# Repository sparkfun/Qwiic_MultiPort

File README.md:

Qwiic MultiPort
========================================

[*SparkFun Qwiic MultiPort (BOB-18012)*](https://www.sparkfun.com/products/18012)

Qwiic is a very efficient way to quickly prototype an idea but not all Qwiic-enabled devices have two ports. The SparkFun Qwiic MultiPort adds additional ports to boards that have only one Qwiic port on the I2C bus. Once added, you can use it as a hub to add as many I2C devices to the bus as you need! Included are mounting holes so that the board can be secured to any system.

Repository Contents
-------------------

* **/Hardware** - Eagle design files (.brd, .sch)
* **/Production** - Production panel files (.brd)

Documentation
--------------
* **[Hookup Guide](https://learn.sparkfun.com/tutorials/1659)**

Product Versions
----------------
* [BOB-18012](https://www.sparkfun.com/products/18012) - Initial Release

License Information
-------------------

This product is _**open source**_! 

Please review the LICENSE.md file for license information. 

If you have any questions or concerns on licensing, please contact technical support on our [SparkFun forums](https://forum.sparkfun.com/viewforum.php?f=152).

Distributed as-is; no warranty is given.

- Your friends at SparkFun.

_<COLLABORATION CREDIT>_

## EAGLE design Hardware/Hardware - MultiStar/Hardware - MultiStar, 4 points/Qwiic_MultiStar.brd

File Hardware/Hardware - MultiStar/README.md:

Qwiic MultiStar
========================================

[*SparkFun Qwiic MultiStar (BOB-?????)*](https://www.sparkfun.com/news/3803)

The MultiStar was designed for April Fools' Day! This board functions like the MultiPort but with an additional Qwiic connector. The board is also shaped like a Ninja star! The following folders include the Eagle files for the MultiStar. For more information, check out the blog post under "[A Sneak Preview of Our Latest Qwiic Product](https://www.sparkfun.com/news/3803)."

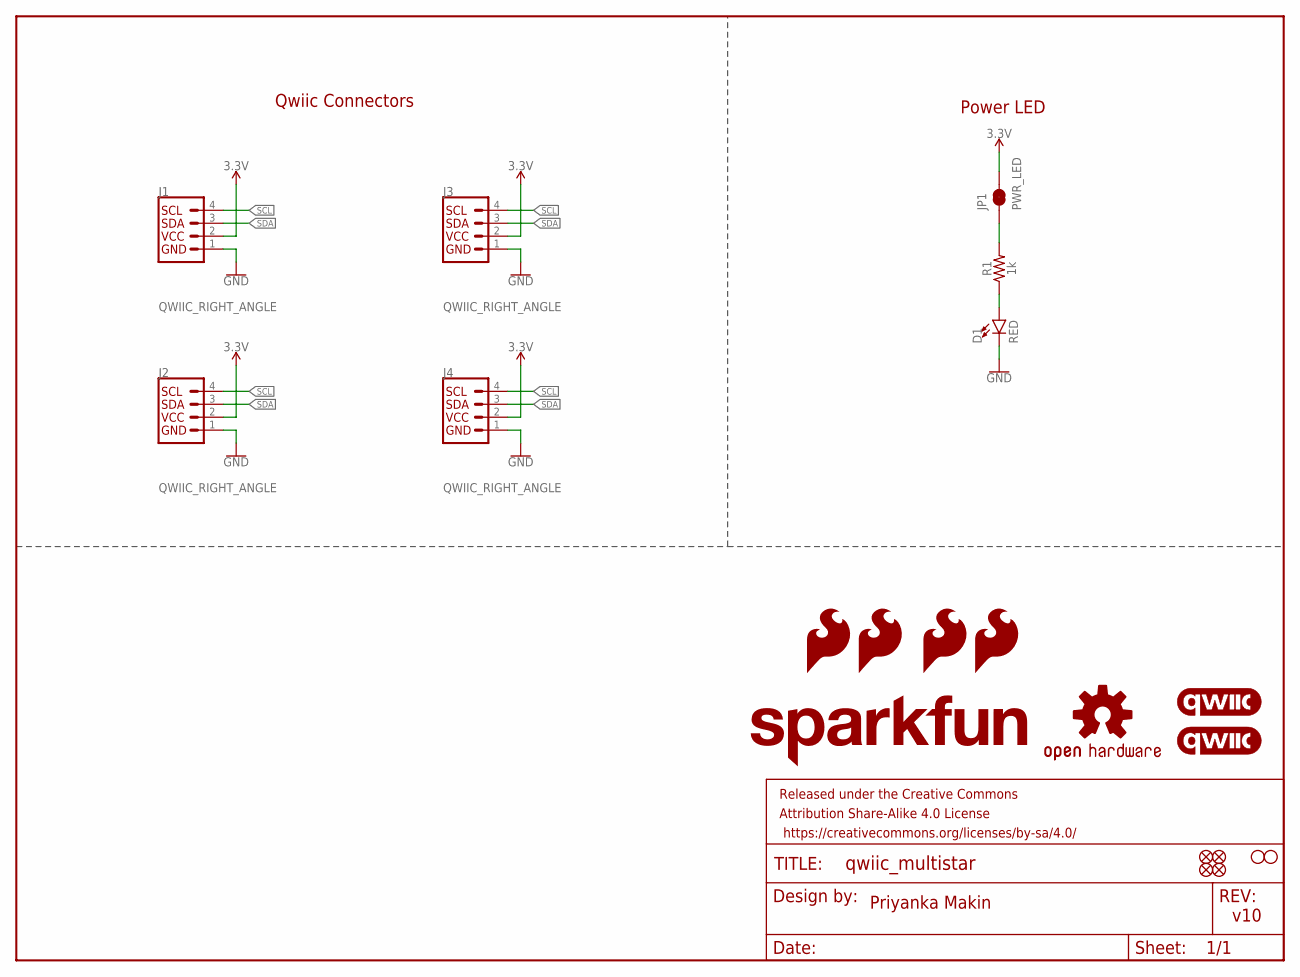
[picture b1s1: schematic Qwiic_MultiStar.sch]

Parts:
D1: RED; LED-0603
FD1, FD2, FD3, FD4: FIDUCIAL1X2; FIDUCIAL-1X2
FRAME1: FRAME-LETTER; CREATIVE_COMMONS
H1, H2: STAND-OFFTIGHT; STAND-OFF-TIGHT
J1, J2, J3, J4: QWIIC_RIGHT_ANGLE; JST04_1MM_RA
JP1: PWR_LED; SMT-JUMPER_2_NC_TRACE_SILK
LOGO1, LOGO2: QWIIC_LOGO_5MM; QWIIC_5MM
LOGO3: OSHW-LOGOS; OSHW-LOGO-S
LOGO4: SFE_LOGO_NAME.2_INCH; SFE_LOGO_NAME_.2
LOGO5, LOGO6, LOGO7, LOGO8: SFE_LOGO_FLAME.1_INCH; SFE_LOGO_FLAME_.1
R1: 1k; 0603

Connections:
3.3V: J1.2, J2.2, J3.2, J4.2, JP1.2
GND: D1.C, J1.1, J2.1, J3.1, J4.1
unnamed: D1.A, R1.1
unnamed: JP1.1, R1.2
SCL: J1.4, J2.4, J3.4, J4.4
SDA: J1.3, J2.3, J3.3, J4.3

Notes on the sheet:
Priyanka Makin
v10
Qwiic Connectors
Power LED

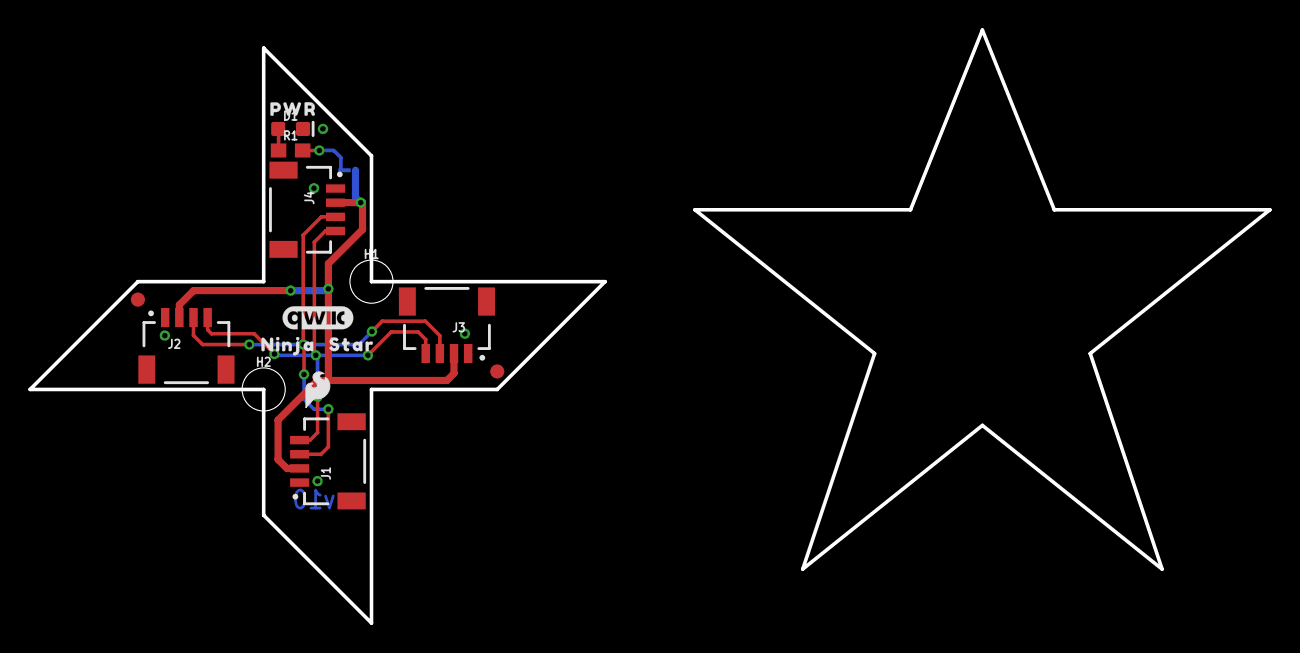
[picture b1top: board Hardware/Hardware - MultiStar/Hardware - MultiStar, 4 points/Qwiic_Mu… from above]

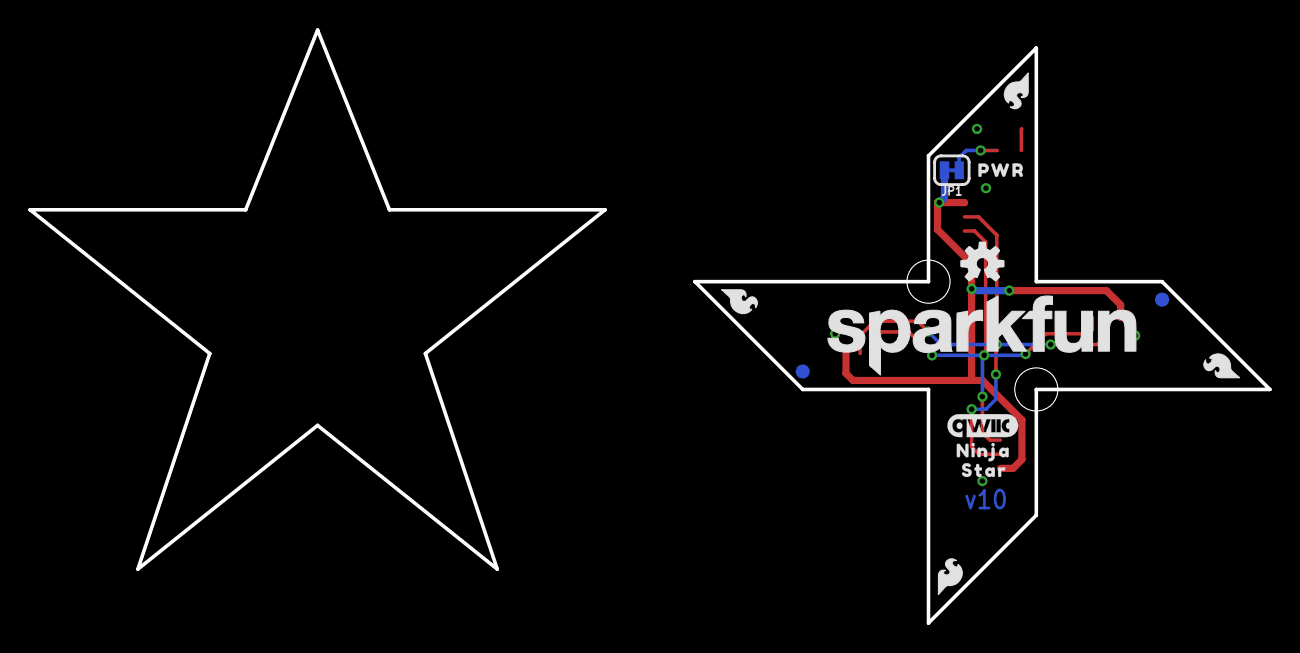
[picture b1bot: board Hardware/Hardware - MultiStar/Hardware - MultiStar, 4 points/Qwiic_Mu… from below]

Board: 2 copper layers, 40.6 x 40.6 mm, 29 parts (13 on the bottom side), 6 nets.

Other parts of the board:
U$2: SFE_LOGO_FLAME_.1
U$3, U$5: NINJA0
U$4, U$9: PWR0
U$6, U$7: STAR0

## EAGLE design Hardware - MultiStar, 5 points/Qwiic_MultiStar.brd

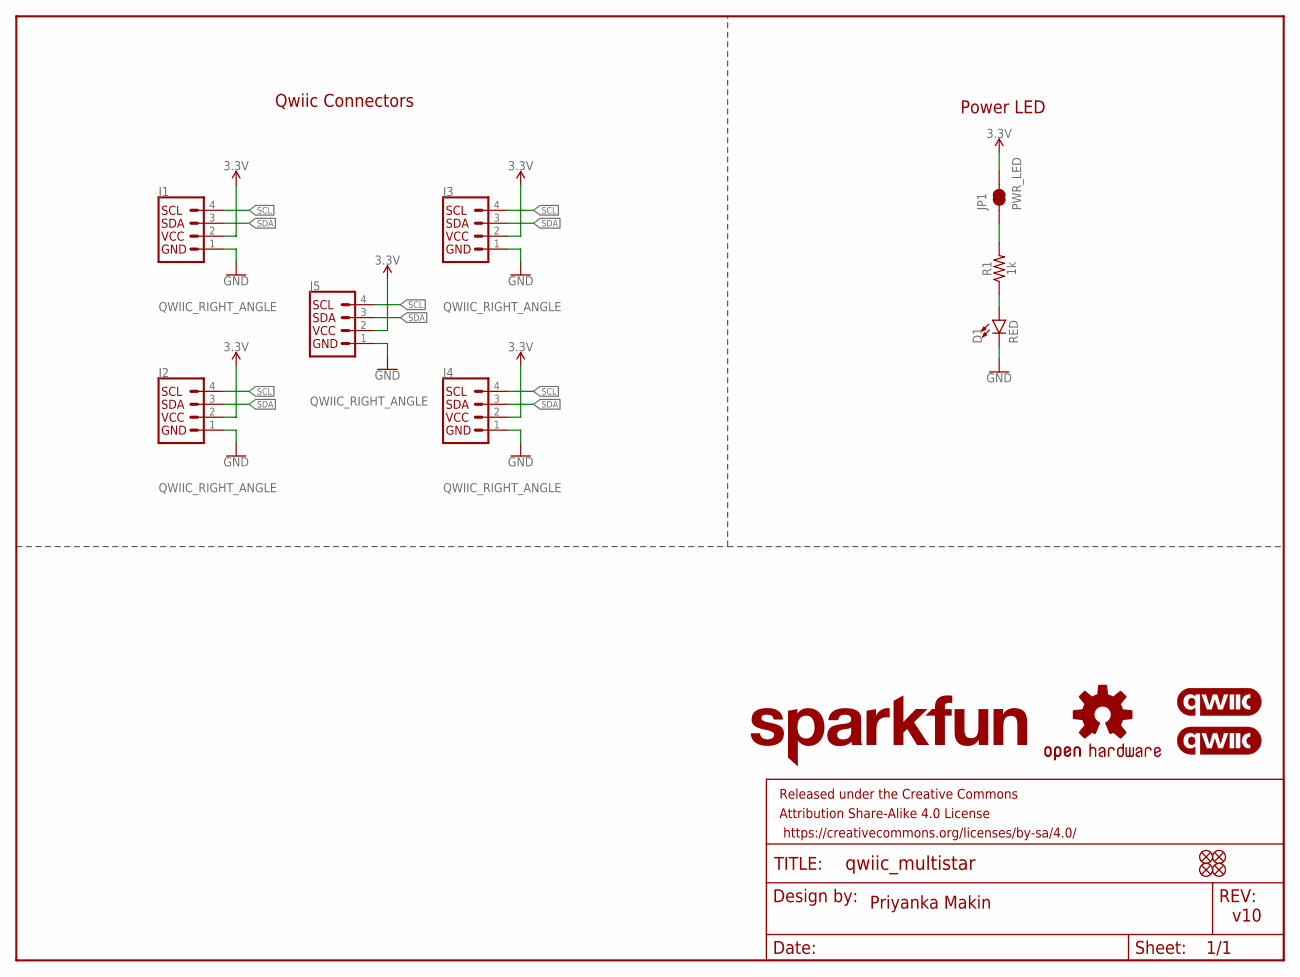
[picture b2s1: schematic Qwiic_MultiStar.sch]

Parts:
D1: RED; LED-0603
FD1, FD2, FD3, FD4: FIDUCIAL1X2; FIDUCIAL-1X2
FRAME1: FRAME-LETTER; CREATIVE_COMMONS
J1, J2, J3, J4, J5: QWIIC_RIGHT_ANGLE; JST04_1MM_RA
JP1: PWR_LED; SMT-JUMPER_2_NC_TRACE_SILK
LOGO1, LOGO2: QWIIC_LOGO_5MM; QWIIC_5MM
LOGO3: OSHW-LOGOS; OSHW-LOGO-S
LOGO4: SFE_LOGO_NAME.2_INCH; SFE_LOGO_NAME_.2
R1: 1k; 0603

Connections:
3.3V: J1.2, J2.2, J3.2, J4.2, J5.2, JP1.2
GND: D1.C, J1.1, J2.1, J3.1, J4.1, J5.1
unnamed: D1.A, R1.1
unnamed: JP1.1, R1.2
SCL: J1.4, J2.4, J3.4, J4.4, J5.4
SDA: J1.3, J2.3, J3.3, J4.3, J5.3

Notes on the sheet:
Priyanka Makin
v10
Qwiic Connectors
Power LED

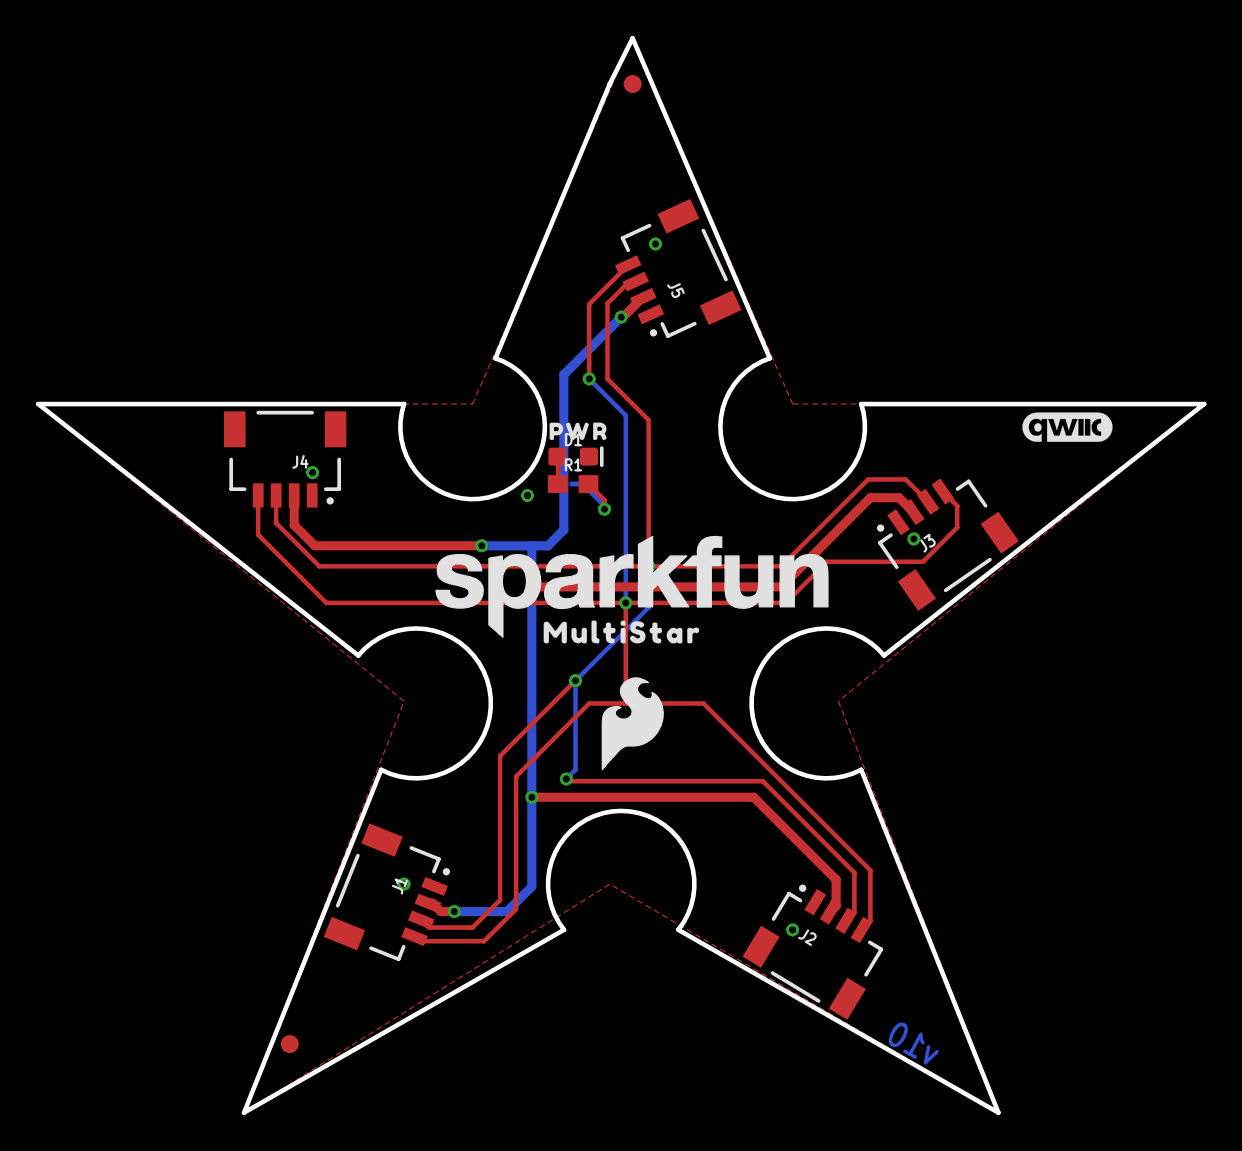
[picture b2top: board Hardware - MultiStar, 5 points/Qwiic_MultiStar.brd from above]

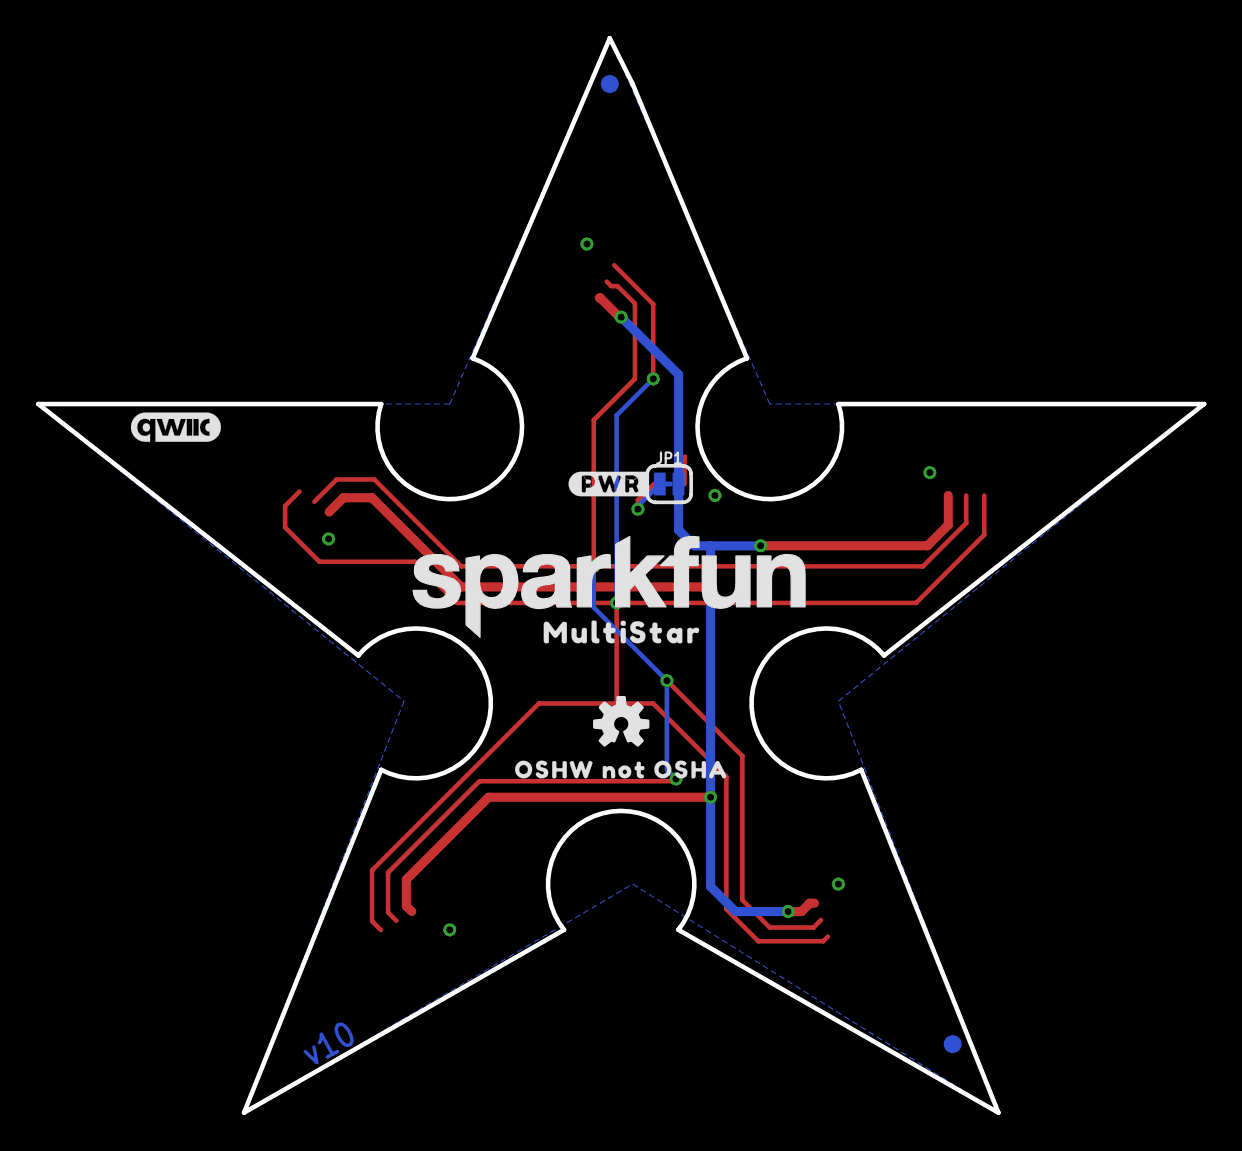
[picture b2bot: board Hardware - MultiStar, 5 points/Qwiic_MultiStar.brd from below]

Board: 2 copper layers, 64.8 x 59.7 mm, 24 parts (9 on the bottom side), 6 nets.

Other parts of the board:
LOGO5: SFE_LOGO_NAME.2_INCH; SFE_LOGO_NAME_.2
U$1: OSHW_NOT_OSHA0
U$2: SFE_LOGO_FLAME_.2
U$3, U$5: MULTISTAR0
U$6: #PWR#0
U$9: PWR0

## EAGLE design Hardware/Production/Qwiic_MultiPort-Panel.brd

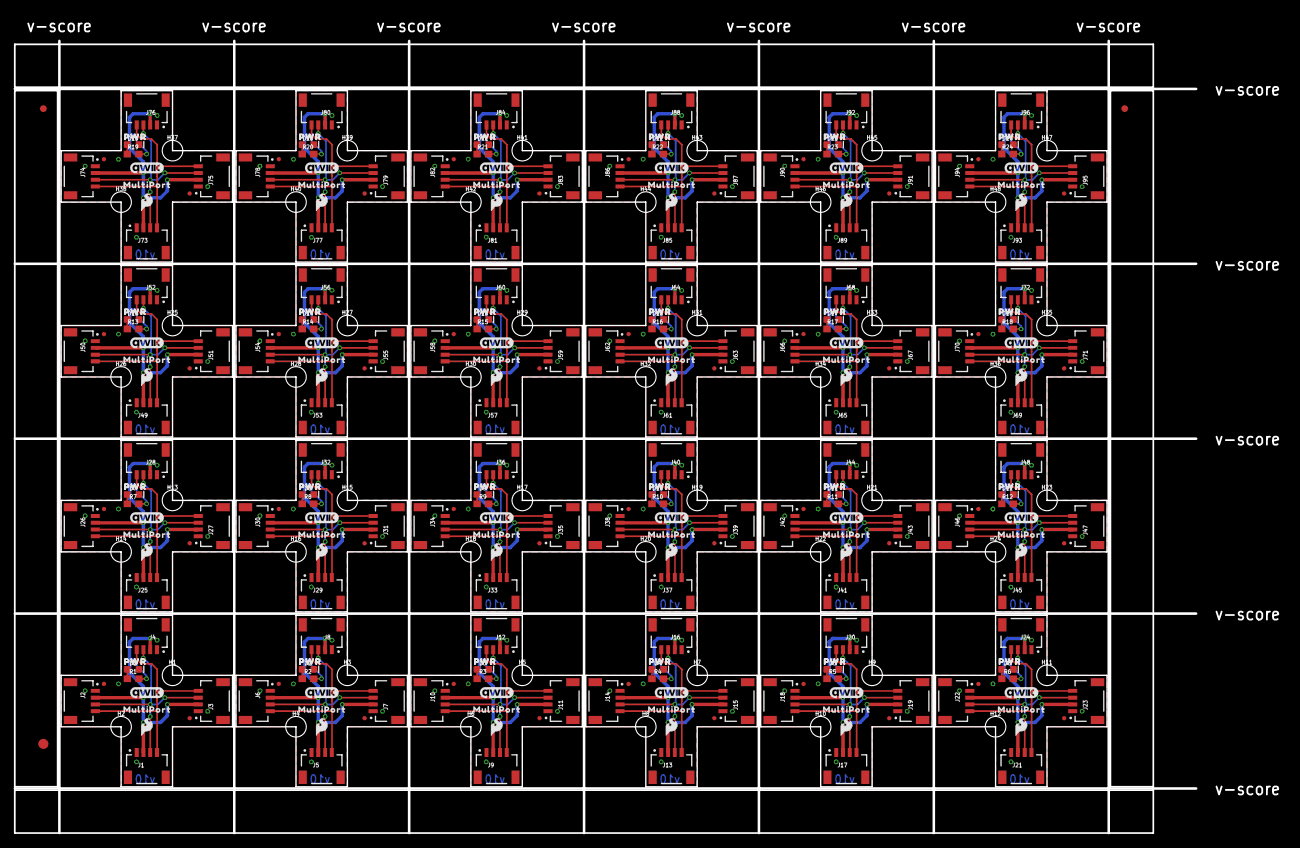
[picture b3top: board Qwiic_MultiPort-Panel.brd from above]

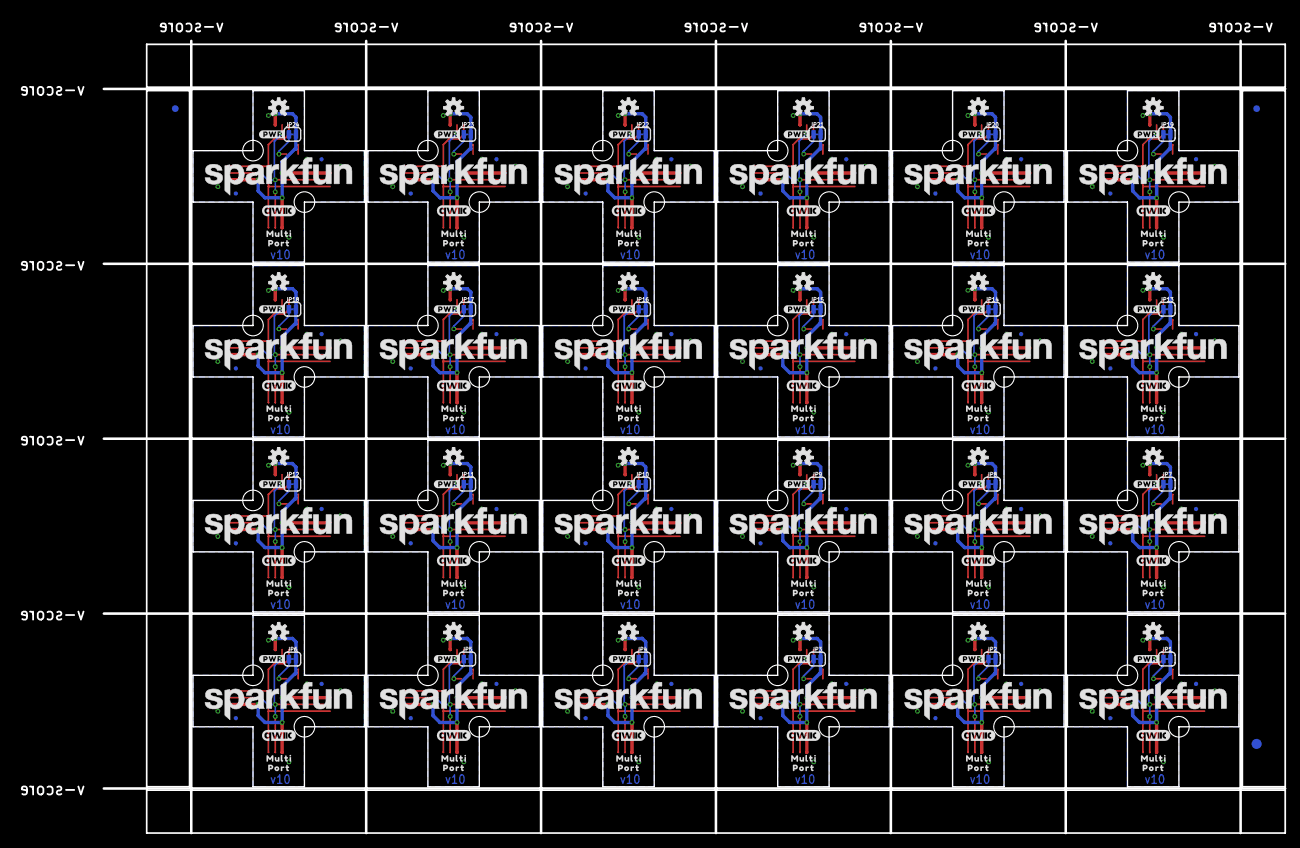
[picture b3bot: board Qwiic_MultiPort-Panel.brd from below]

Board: 2 copper layers, 175.0 x 117.3 mm, 582 parts (219 on the bottom side), 144 nets.

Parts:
D1, D2, D3, D4, D5, D6, D7, D8, D9, D10, D11, D12, D13, D14, D15, D16, D17, D18, D19, D20, D21, D22, D23, D24: RED; LED-0603
E$1, E$2, E$3, E$4: FIDUCIAL-1X2
E$5, E$6: FIDUCIAL-1.5X3
FD1, FD2, FD3, FD4, FD5, FD6, FD7, FD8, FD9, FD10, FD11, FD12, FD13, FD14, FD15, FD16, FD17, FD18, FD19, FD20, FD21, FD22, FD23, FD24, FD25, FD26, FD27, FD28, FD29, FD30, FD31, FD32, FD33, FD34, FD35, FD36, FD37, FD38, FD39, FD40, FD41, FD42, FD43, FD44, FD45, FD46, FD47, FD48, FD49, FD50, FD51, FD52, FD53, FD54, FD55, FD56, FD57, FD58, FD59, FD60, FD61, FD62, FD63, FD64, FD65, FD66, FD67, FD68, FD69, FD70, FD71, FD72, FD73, FD74, FD75, FD76, FD77, FD78, FD79, FD80, FD81, FD82, FD83, FD84, FD85, FD86, FD87, FD88, FD89, FD90, FD91, FD92, FD93, FD94, FD95, FD96: FIDUCIALUFIDUCIAL; FIDUCIAL-MICRO
H1, H2, H3, H4, H5, H6, H7, H8, H9, H10, H11, H12, H13, H14, H15, H16, H17, H18, H19, H20, H21, H22, H23, H24, H25, H26, H27, H28, H29, H30, H31, H32, H33, H34, H35, H36, H37, H38, H39, H40, H41, H42, H43, H44, H45, H46, H47, H48: STAND-OFFTIGHT; STAND-OFF-TIGHT
J1, J2, J3, J4, J5, J6, J7, J8, J9, J10, J11, J12, J13, J14, J15, J16, J17, J18, J19, J20, J21, J22, J23, J24, J25, J26, J27, J28, J29, J30, J31, J32, J33, J34, J35, J36, J37, J38, J39, J40, J41, J42, J43, J44, J45, J46, J47, J48, J49, J50, J51, J52, J53, J54, J55, J56, J57, J58, J59, J60, J61, J62, J63, J64, J65, J66, J67, J68, J69, J70, J71, J72, J73, J74, J75, J76, J77, J78, J79, J80, J81, J82, J83, J84, J85, J86, J87, J88, J89, J90, J91, J92, J93, J94, J95, J96: QWIIC_RIGHT_ANGLE; JST04_1MM_RA
JP1, JP2, JP3, JP4, JP5, JP6, JP7, JP8, JP9, JP10, JP11, JP12, JP13, JP14, JP15, JP16, JP17, JP18, JP19, JP20, JP21, JP22, JP23, JP24: PWR_LED; SMT-JUMPER_2_NC_TRACE_SILK
LOGO1, LOGO2, LOGO5, LOGO6, LOGO9, LOGO10, LOGO13, LOGO14, LOGO17, LOGO18, LOGO21, LOGO22, LOGO25, LOGO26, LOGO29, LOGO30, LOGO33, LOGO34, LOGO37, LOGO38, LOGO41, LOGO42, LOGO45, LOGO46, LOGO49, LOGO50, LOGO53, LOGO54, LOGO57, LOGO58, LOGO61, LOGO62, LOGO65, LOGO66, LOGO69, LOGO70, LOGO73, LOGO74, LOGO77, LOGO78, LOGO81, LOGO82, LOGO85, LOGO86, LOGO89, LOGO90, LOGO93, LOGO94: QWIIC_LOGO_5MM; QWIIC_5MM
LOGO3, LOGO7, LOGO11, LOGO15, LOGO19, LOGO23, LOGO27, LOGO31, LOGO35, LOGO39, LOGO43, LOGO47, LOGO51, LOGO55, LOGO59, LOGO63, LOGO67, LOGO71, LOGO75, LOGO79, LOGO83, LOGO87, LOGO91, LOGO95: OSHW-LOGOS; OSHW-LOGO-S
LOGO4, LOGO8, LOGO12, LOGO16, LOGO20, LOGO24, LOGO28, LOGO32, LOGO36, LOGO40, LOGO44, LOGO48, LOGO52, LOGO56, LOGO60, LOGO64, LOGO68, LOGO72, LOGO76, LOGO80, LOGO84, LOGO88, LOGO92, LOGO96: SFE_LOGO_NAME.2_INCH; SFE_LOGO_NAME_.2
R1, R2, R3, R4, R5, R6, R7, R8, R9, R10, R11, R12, R13, R14, R15, R16, R17, R18, R19, R20, R21, R22, R23, R24: 1k; 0603
U$1, U$6, U$9, U$10, U$16, U$19, U$23, U$26, U$30, U$33, U$37, U$40, U$44, U$47, U$51, U$54, U$58, U$61, U$65, U$68, U$72, U$75, U$79, U$82, U$86, U$89, U$93, U$96, U$100, U$103, U$107, U$110, U$114, U$117, U$121, U$124, U$128, U$131, U$135, U$138, U$142, U$145, U$149, U$152, U$156, U$159, U$163, U$166: PWR0
U$2, U$3, U$15, U$22, U$29, U$36, U$43, U$50, U$57, U$64, U$71, U$78, U$85, U$92, U$99, U$106, U$113, U$120, U$127, U$134, U$141, U$148, U$155, U$162: SFE_LOGO_FLAME_.1
U$4, U$12, U$20, U$27, U$34, U$41, U$48, U$55, U$62, U$69, U$76, U$83, U$90, U$97, U$104, U$111, U$118, U$125, U$132, U$139, U$146, U$153, U$160, U$167: MULTIPORT0
U$5, U$14, U$21, U$28, U$35, U$42, U$49, U$56, U$63, U$70, U$77, U$84, U$91, U$98, U$105, U$112, U$119, U$126, U$133, U$140, U$147, U$154, U$161, U$168: #PWR#0
U$7, U$11, U$17, U$24, U$31, U$38, U$45, U$52, U$59, U$66, U$73, U$80, U$87, U$94, U$101, U$108, U$115, U$122, U$129, U$136, U$143, U$150, U$157, U$164: MULTI0
U$8, U$13, U$18, U$25, U$32, U$39, U$46, U$53, U$60, U$67, U$74, U$81, U$88, U$95, U$102, U$109, U$116, U$123, U$130, U$137, U$144, U$151, U$158, U$165: PORT0

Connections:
3.3V: J1.2, J2.2, J3.2, J4.2, JP1.2
3.3V1: J5.2, J6.2, J7.2, J8.2, JP2.2
3.3V2: J9.2, J10.2, J11.2, J12.2, JP3.2
3.3V3: J13.2, J14.2, J15.2, J16.2, JP4.2
3.3V4: J17.2, J18.2, J19.2, J20.2, JP5.2
3.3V5: J21.2, J22.2, J23.2, J24.2, JP6.2
3.3V6: J25.2, J26.2, J27.2, J28.2, JP7.2
3.3V7: J29.2, J30.2, J31.2, J32.2, JP8.2
3.3V8: J33.2, J34.2, J35.2, J36.2, JP9.2
3.3V9: J37.2, J38.2, J39.2, J40.2, JP10.2
3.3V10: J41.2, J42.2, J43.2, J44.2, JP11.2
3.3V11: J45.2, J46.2, J47.2, J48.2, JP12.2
3.3V12: J49.2, J50.2, J51.2, J52.2, JP13.2
3.3V13: J53.2, J54.2, J55.2, J56.2, JP14.2
3.3V14: J57.2, J58.2, J59.2, J60.2, JP15.2
3.3V15: J61.2, J62.2, J63.2, J64.2, JP16.2
3.3V16: J65.2, J66.2, J67.2, J68.2, JP17.2
3.3V17: J69.2, J70.2, J71.2, J72.2, JP18.2
3.3V18: J73.2, J74.2, J75.2, J76.2, JP19.2
3.3V19: J77.2, J78.2, J79.2, J80.2, JP20.2
3.3V20: J81.2, J82.2, J83.2, J84.2, JP21.2
3.3V21: J85.2, J86.2, J87.2, J88.2, JP22.2
3.3V22: J89.2, J90.2, J91.2, J92.2, JP23.2
3.3V23: J93.2, J94.2, J95.2, J96.2, JP24.2
GND: D1.C, J1.1, J2.1, J3.1, J4.1
GND1: D2.C, J5.1, J6.1, J7.1, J8.1
GND2: D3.C, J9.1, J10.1, J11.1, J12.1
GND3: D4.C, J13.1, J14.1, J15.1, J16.1
GND4: D5.C, J17.1, J18.1, J19.1, J20.1
GND5: D6.C, J21.1, J22.1, J23.1, J24.1
GND6: D7.C, J25.1, J26.1, J27.1, J28.1
GND7: D8.C, J29.1, J30.1, J31.1, J32.1
GND8: D9.C, J33.1, J34.1, J35.1, J36.1
GND9: D10.C, J37.1, J38.1, J39.1, J40.1
GND10: D11.C, J41.1, J42.1, J43.1, J44.1
GND11: D12.C, J45.1, J46.1, J47.1, J48.1
GND12: D13.C, J49.1, J50.1, J51.1, J52.1
GND13: D14.C, J53.1, J54.1, J55.1, J56.1
GND14: D15.C, J57.1, J58.1, J59.1, J60.1
GND15: D16.C, J61.1, J62.1, J63.1, J64.1
GND16: D17.C, J65.1, J66.1, J67.1, J68.1
GND17: D18.C, J69.1, J70.1, J71.1, J72.1
GND18: D19.C, J73.1, J74.1, J75.1, J76.1
GND19: D20.C, J77.1, J78.1, J79.1, J80.1
GND20: D21.C, J81.1, J82.1, J83.1, J84.1
GND21: D22.C, J85.1, J86.1, J87.1, J88.1
GND22: D23.C, J89.1, J90.1, J91.1, J92.1
GND23: D24.C, J93.1, J94.1, J95.1, J96.1
unnamed: D1.A, R1.1
unnamed: JP1.1, R1.2
unnamed: D2.A, R2.1
unnamed: JP2.1, R2.2
unnamed: D3.A, R3.1
unnamed: JP3.1, R3.2
unnamed: D4.A, R4.1
unnamed: JP4.1, R4.2
unnamed: D5.A, R5.1
unnamed: JP5.1, R5.2
unnamed: D6.A, R6.1
unnamed: JP6.1, R6.2
unnamed: D7.A, R7.1
unnamed: JP7.1, R7.2
unnamed: D8.A, R8.1
unnamed: JP8.1, R8.2
unnamed: D9.A, R9.1
unnamed: JP9.1, R9.2
unnamed: D10.A, R10.1
unnamed: JP10.1, R10.2
unnamed: D11.A, R11.1
unnamed: JP11.1, R11.2
unnamed: D12.A, R12.1
unnamed: JP12.1, R12.2
unnamed: D13.A, R13.1
unnamed: JP13.1, R13.2
unnamed: D14.A, R14.1
unnamed: JP14.1, R14.2
unnamed: D15.A, R15.1
unnamed: JP15.1, R15.2
unnamed: D16.A, R16.1
unnamed: JP16.1, R16.2
unnamed: D17.A, R17.1
unnamed: JP17.1, R17.2
unnamed: D18.A, R18.1
unnamed: JP18.1, R18.2
unnamed: D19.A, R19.1
unnamed: JP19.1, R19.2
unnamed: D20.A, R20.1
unnamed: JP20.1, R20.2
unnamed: D21.A, R21.1
unnamed: JP21.1, R21.2
unnamed: D22.A, R22.1
unnamed: JP22.1, R22.2
unnamed: D23.A, R23.1
unnamed: JP23.1, R23.2
unnamed: D24.A, R24.1
unnamed: JP24.1, R24.2
SCL: J1.4, J2.4, J3.4, J4.4
SCL1: J5.4, J6.4, J7.4, J8.4
SCL2: J9.4, J10.4, J11.4, J12.4
SCL3: J13.4, J14.4, J15.4, J16.4
SCL4: J17.4, J18.4, J19.4, J20.4
SCL5: J21.4, J22.4, J23.4, J24.4
SCL6: J25.4, J26.4, J27.4, J28.4
SCL7: J29.4, J30.4, J31.4, J32.4
SCL8: J33.4, J34.4, J35.4, J36.4
SCL9: J37.4, J38.4, J39.4, J40.4
SCL10: J41.4, J42.4, J43.4, J44.4
SCL11: J45.4, J46.4, J47.4, J48.4
SCL12: J49.4, J50.4, J51.4, J52.4
SCL13: J53.4, J54.4, J55.4, J56.4
SCL14: J57.4, J58.4, J59.4, J60.4
SCL15: J61.4, J62.4, J63.4, J64.4
SCL16: J65.4, J66.4, J67.4, J68.4
SCL17: J69.4, J70.4, J71.4, J72.4
SCL18: J73.4, J74.4, J75.4, J76.4
SCL19: J77.4, J78.4, J79.4, J80.4
SCL20: J81.4, J82.4, J83.4, J84.4
SCL21: J85.4, J86.4, J87.4, J88.4
SCL22: J89.4, J90.4, J91.4, J92.4
SCL23: J93.4, J94.4, J95.4, J96.4
SDA: J1.3, J2.3, J3.3, J4.3
SDA1: J5.3, J6.3, J7.3, J8.3
SDA2: J9.3, J10.3, J11.3, J12.3
SDA3: J13.3, J14.3, J15.3, J16.3
SDA4: J17.3, J18.3, J19.3, J20.3
SDA5: J21.3, J22.3, J23.3, J24.3
SDA6: J25.3, J26.3, J27.3, J28.3
SDA7: J29.3, J30.3, J31.3, J32.3
SDA8: J33.3, J34.3, J35.3, J36.3
SDA9: J37.3, J38.3, J39.3, J40.3
SDA10: J41.3, J42.3, J43.3, J44.3
SDA11: J45.3, J46.3, J47.3, J48.3
SDA12: J49.3, J50.3, J51.3, J52.3
SDA13: J53.3, J54.3, J55.3, J56.3
SDA14: J57.3, J58.3, J59.3, J60.3
SDA15: J61.3, J62.3, J63.3, J64.3
SDA16: J65.3, J66.3, J67.3, J68.3
SDA17: J69.3, J70.3, J71.3, J72.3
SDA18: J73.3, J74.3, J75.3, J76.3
SDA19: J77.3, J78.3, J79.3, J80.3
SDA20: J81.3, J82.3, J83.3, J84.3
SDA21: J85.3, J86.3, J87.3, J88.3
SDA22: J89.3, J90.3, J91.3, J92.3
SDA23: J93.3, J94.3, J95.3, J96.3

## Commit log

2021-02-08 Add power LED to board
2021-02-08 Update SFE logos on board
2021-02-08 Update silk screen
2021-02-08 Update silkscreen
2021-02-09 Created Qwiic Ninja Star
2021-02-10 Multi Port: Design Review Changes
    Added jumper on PWR LED
    Added fiducials
    Added OSHW, qwiic, SF logo as device on the schematic
    Moved traces on top layer to avoid screws
    Decided against:
    un-populated I2C pullups -- not enough space
2021-02-10 Ninja Star: Design Review Changes
    Added jumper to PWR LED
    Added fiducials
    Added OSHW, qwiic, SF, and flame logo devices to schematic
    Tried my best to move traces out from underneath screws
2021-02-10 Update silkscreen name to "Ninja Star"
2021-02-10 Completed Engineering checklist
2021-02-15 Created star-shaped Qwiic Ninja Star and updated Multi Port
    Updated Qwiic Multi Port with QC Double check concerns:
    Removed wire stub
    Approve DRC errors
    Move via to not clip the t in "Port" on top
    Moved power jumper and silk so that jumper silk and SF logo don't overlap
2021-02-16 Panelized
2021-02-16 Wired qwiic ninja star
2021-02-16 Renamed the boards to CamelCase
    Multi Port --> MultiPort
    Ninja Star --> MultiStar
2021-02-17 MultiPort - Pete's notes
    Reduced fiducial size to Micro
    Moved PWR LED jumper and generated inverted label for jumper
2021-02-17 MultiPort - re-panelized
2021-02-18 re-route MultiPort in daisy chain configuration
2021-02-18 Re-panelized Qwiic MultiPort
    Less than 7x5 inches
2021-02-19 Generate gerbers for Qwiic MultiStar
2021-04-01 Moving MultiStar into Subfolder

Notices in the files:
parts and their libraries:
SparkFun-Connectors: Licensing: Creative Commons ShareAlike 4.0 International - https://creativecommons.org/licenses/by-sa/4.0
SparkFun-Aesthetics: Released under the Creative Commons Attribution Share-Alike 4.0 License
SparkFun-Aesthetics: https://creativecommons.org/licenses/by-sa/4.0
